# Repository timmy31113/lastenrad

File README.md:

# lastenrad
Control system for a prototype cargo bike with a bio-electric hybrid drivetrain concept

This project contains the code for an Arduino controlling the electric systems of a three wheeled Dutch-style cargo bike. 

- A synchronous permanently commutated three-phase AC hub motor drives the rear wheel. 
It is powered by an external motor controller with current and movement direction control.
The motor and controller also allow a regenerative braking function.

- The cyclists pedals into a synchronous permanently commutated three-phase AC generator with a gear transmission.
The generator load is regulated by a power-MOSFET performing PWM after rectification. 
A current sensor indicates how much power the cyclist is putting into the generator.

- The UI provides adjustment options for the desired degree of electric assist and the target pedaling RPM and torque.

The system aims to simulate an automatic CVT gearbox and the goal is an intuitive and comfortable driving experience 
that allows the cyclist to concentrate on the road situation while maintaining optimal power delivery to the wheel.

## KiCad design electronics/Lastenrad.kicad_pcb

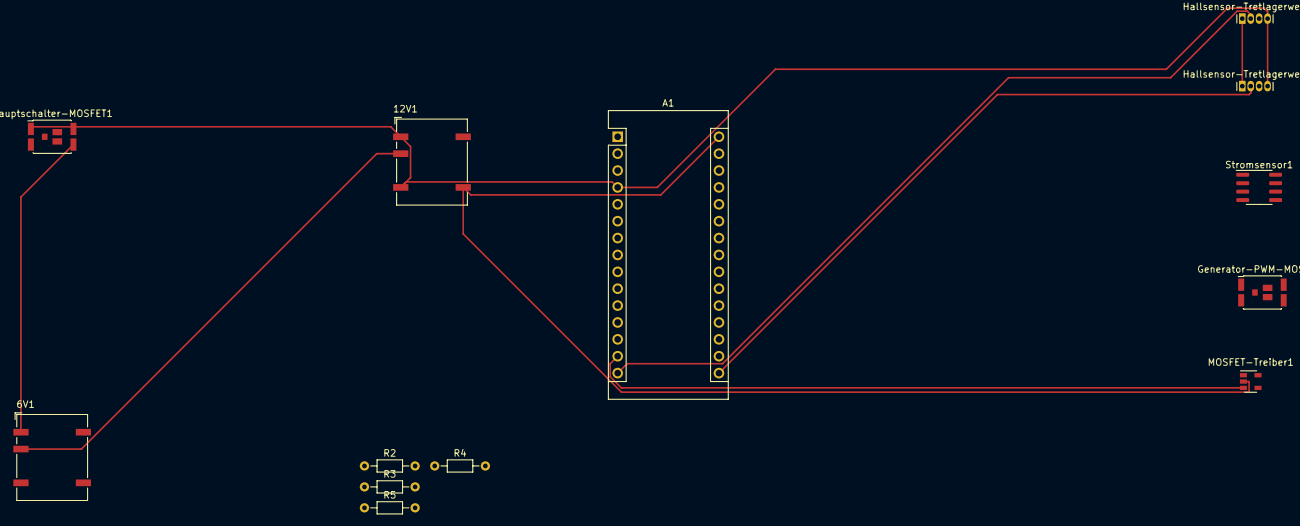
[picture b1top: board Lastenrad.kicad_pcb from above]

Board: 2 copper layers, 13 parts (0 on the bottom side), 14 nets.

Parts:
6V1, 12V1: NXE2S1215MC; Converter_DCDC_muRata_NXExSxxxxMC_SMD
A1: Arduino_Nano_v3.x; Arduino_Nano
Generator-PWM-MOSFET1: BSB044N08NN3; DirectFET_MN
Hallsensor-Tretlagerwelle-1, Hallsensor-Tretlagerwelle-2: A1363xKTTN-1; Allegro_SIP-4
Hauptschalter-MOSFET1: BSB044N08NN3; DirectFET_MN
MOSFET-Treiber1: MCP1416; SOT-23-5
R2, R4: 100k; R_Axial_DIN0204_L3.6mm_D1.6mm_P7.62mm_Horizontal
R3, R5: 47k; R_Axial_DIN0204_L3.6mm_D1.6mm_P7.62mm_Horizontal
Stromsensor1: ACS712xLCTR-05B; SOIC-8_3.9x4.9mm_P1.27mm

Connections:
GND: 6V1.1, 6V1.7, 12V1.1, 12V1.7, A1.29, Generator-PWM-MOSFET1.3, Hallsensor-Tretlagerwelle-1.4, Hallsensor-Tretlagerwelle-2.4, Hauptschalter-MOSFET1.1, MOSFET-Treiber1.4, R3.2, R5.2, Stromsensor1.5
unnamed: 6V1.3, 12V1.3
unnamed: 12V1.8, A1.30, MOSFET-Treiber1.2
unnamed: A1.5, R4.2, R5.1
unnamed: A1.10, R2.2, R3.1
unnamed: A1.14, MOSFET-Treiber1.3
unnamed: A1.15, Hallsensor-Tretlagerwelle-2.2
unnamed: A1.16, Hallsensor-Tretlagerwelle-1.2
unnamed: A1.19, Stromsensor1.7
unnamed: A1.27, Hallsensor-Tretlagerwelle-1.1, Hallsensor-Tretlagerwelle-2.1, Stromsensor1.8
unnamed: Stromsensor1.1, Stromsensor1.2
unnamed: Generator-PWM-MOSFET1.1, Stromsensor1.3, Stromsensor1.4
unnamed: Generator-PWM-MOSFET1.2, MOSFET-Treiber1.5
unnamed: R2.1, R4.1

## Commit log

2021-05-04 Initial commit
    Moved the project to git.
2021-05-04 Changed directory structure
    Moved Lastenrad.ino to subdirectory Lastenrad.
2021-05-06 Changed generator pinout
    The generator now uses only two sensors. The two now-free additional pins are reserved for future add-ons and are physically linked up to the dashboard connector. This commit reflects that design cha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
2021-06-15 Changed the power control
    Output power of the motor is now calculated depending on speed, torque,
    current and voltage. This ensures that the motor never puts out more
    power than legally allowed, while at the same time still allowing a
    reasonably high current in low efficiency situations (accelerating from a
    standstill or on steep grades).
2023-09-11 Added circuit diagrams to version control
2025-05-29 Updated circuit diagrams file format version
    From version 3 to version 5
2025-05-29 Circuit diagram: Moved motor and motor controller
    Slight adjustments to the positioning to make the connection between
    different physical section more clear
2025-07-06 Circuit diagram: Resistor values
    My dad added sensible resistor values all around the circuit diagram
2025-07-06 gitignore: New KiCad backup files are now ignored
